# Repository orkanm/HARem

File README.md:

# HARem - Home Assistant Remote Controller

**HARem** is a high-performance, minimalist "Thin Client" remote controller designed for the modern smart home. Built on the **ESPHome** ecosystem and powered by the **ESP32-C3**, it provides a boutique-quality physical interface that prioritizes speed, aesthetics, and zero-maintenance operation.

---

## ✨ Features & Architecture

Unlike traditional smart remotes that require manual configuration of every button, HARem operates as a **dynamic viewport** into your Home Assistant instance. Complex logic is handled by Home Assistant Blueprints and Automations, keeping the hardware lightweight and responsive.

- **Zero Maintenance**: Rooms, devices, and states are streamed in real-time. New devices added to a Home Assistant Area automatically appear on the remote.
- **Modern UI**: A 5-line **1.3" OLED** interface featuring Outfit and Montserrat typography, a vertical scrollbar, and hardware-accelerated dynamic marquee for long names.
- **Smart Power**: Deep sleep optimized for sub-1mA idle consumption, utilizing a high-impedance (1MΩ/1MΩ) battery divider and active OLED power management.
- **Guest Mode Protection**: Secure, PIN-protected "Guest Mode" to restrict access to specific areas or devices.
- **Visual Feedback & Control**: Interactive animations, sleep countdowns, and a local on-device menu for contrast and standby settings.

---

## 🚀 Quick Start

1. **Hardware**: ESP32-C3 SuperMini + 1.3" SH1106 OLED + EC11 Rotary Encoder.
2. **Firmware**: 
    * **Option A (Recommended)**: Download the latest **`.factory.bin`** from [Releases](https://github.com/orkanm/HARem/releases) and flash it to **offset 0x0**.
    * **Option B**: Compile locally using `esphome run remote_controller.yaml`.
3. **Home Assistant**: 
    * The device will appear as "HARem" in your dashboard.
    * **IMPORTANT**: If you used the GitHub Release binary, you will be asked for an **Encryption Key**:
        > `7knRB3/EL4Fq8Foul7Yhv+pcABzyLXHSQxa9bTzzQqg=`
    * > [!WARNING]
      > This key is **publicly known**. For security, you should change it in your own configuration and perform an [OTA update](https://esphome.io/components/ota.html) as soon as possible.
    * Follow the [Setup Guide](docs/generic_menu_setup.md) to create the required Helpers and import the logic Blueprint.

---

## 🛠️ Hardware & Assembly

Building your own HARem is straightforward. The project includes custom PCB files and 3D printable case models.

### Interactive Visualizers
Explore the design files directly in your browser:
* **[Interactive PCB 3D Viewer](https://3dviewer.net/index.html#model=https://raw.githubusercontent.com/orkanm/HARem/main/PCB/HARem/HArem.step)** (STEP format)
* **[Interactive Case 3D Viewer](https://3dviewer.net/index.html#model=https://raw.githubusercontent.com/orkanm/HARem/main/Case/HARem_Case_2.0-Case.stl,https://raw.githubusercontent.com/orkanm/HARem/main/Case/HARem_Case_2.0-Lid.stl,https://raw.githubusercontent.com/orkanm/HARem/main/Case/Encoder_Knob.stl)** (STL format)
* **[Interactive Schematic](https://kicanvas.org/?github=https://github.com/orkanm/HARem/blob/main/PCB/HARem/HArem.kicad_sch)**
* **[Interactive PCB Layout](https://kicanvas.org/?github=https://github.com/orkanm/HARem/blob/main/PCB/HARem/HArem.kicad_pcb)**

### Design Files
* **[KiCad Project](PCB/HARem/)**: Source files for schematic and board layout.
* **[PCB 3D Model](PCB/HARem/HArem.step)**: Industrial standard 3D file for enclosure design.
* **[3D Printed Case Files](Case/)**: Source FreeCAD project (`.FCStd`), print-ready `.stl` files for the case, lid, and knob, along with a high-resolution `.step` model.

<details>
<summary><b>View Wiring Diagram & Pin Mapping (Click to expand)</b></summary>

```text
       ESP32-C3 Super Mini                 Peripherals
    ┌───────────────────────┐            ┌───────────────┐
    │                       │   Q1(NPN)  │ 1.3" OLED     │
    │          5V / 3.3V ───┼────▶[C]    │               │
    │  GPIO1 (OLED PWR) ────┼────▶[B]    │               │
    │                       │     [E]────┼─▶ [VCC]       │
    │                GND ───┼────────────┼─▶ [GND]       │
    │         GPIO5 (SDA)───┼────────────┼─▶ [SDA]       │
    │         GPIO6 (SCL)───┼────────────┼─▶ [SCL]       │
    │                       │            └───────────────┘
    │                       │            
    │                       │            ┌───────────────┐
    │                       │            │ ROTARY (EC11) │
    │         GPIO8 (CLK) ◀─┼───[100Ω]───┼─ [CLK]        │
    │          GPIO9 (DT) ◀─┼───[100Ω]───┼─ [DT]         │
    │          GPIO4 (SW) ◀─┼───[100Ω]───┼─ [SW]         │
    │                GND  ◀─┼────────────┼─ [GND]        │
    │                       │            └───────────────┘
    │                       │            ┌───────────────┐
    │                       │            │ BAT MONITOR   │
    │                       │            │  [+] BATTERY  │
    │                       │            │   │           │
    │                       │            │  [1MΩ]        │
    │         GPIO0 (ADC) ◀─┼────────────┼───┤           │
    │                       │            │  [1MΩ] [0.1µF]│
    │                       │            │   │      │    │
    │                GND  ◀─┼────────────┼──GND────GND   │
    └───────────────────────┘            └───────────────┘
```

| Component | ESP32-C3 Pin | Type | Notes |
| :--- | :--- | :--- | :--- |
| **OLED VCC** | GPIO1 | Output | Active Power Management (via Q1 NPN) |
| **OLED SDA/SCL** | GPIO5 / GPIO6 | I2C | SSD1306/SH1106 |
| **Encoder CLK/DT** | GPIO8 / GPIO9 | Input | Navigation |
| **Encoder SW** | GPIO4 | Input | Wakeup Trigger |
| **Battery ADC** | GPIO0 | Analog | 1M/1M Divider + 0.1µF Cap |

</details>

---

## 📖 Documentation & Development

* **[Behavior & Interaction Map](docs/behavior_map.md)**: Visual state machines and logic flows for the device interaction.
* **[Project Walkthrough](docs/walkthrough.md)**: Architecture, features, and troubleshooting.
* **[Home Assistant Setup Guide](docs/generic_menu_setup.md)**: How to configure the Home Assistant side.
* **[Environment Installation & Setup Guide](docs/installation.md)**: Guide for setting up your local Python environment and secrets.
* **[Roadmap](TODO.md)**: Planned improvements and future features.

---

## 📛 Trivia: The Name HARem

The name **HARem** is a clever portmanteau of **H**ome **A**ssistant and **Rem**ote, but its inspiration runs deeper into Turkish history and culture. 

In Turkish and Ottoman history, the **Harem** represented the most private, sacred, and protected part of the household. By adopting this name, the project acknowledges the smart home as the modern individual's "inner sanctum." Just as the historical Harem was the heart of the home, this remote serves as the private, primary interface to control and protect the sanctity of your living space.

---

## ☕ Support the Project

If you find this project helpful and would like to support its development, you can buy me a coffee! Your support helps fund new prototypes and keeps the project open-source and free for everyone.

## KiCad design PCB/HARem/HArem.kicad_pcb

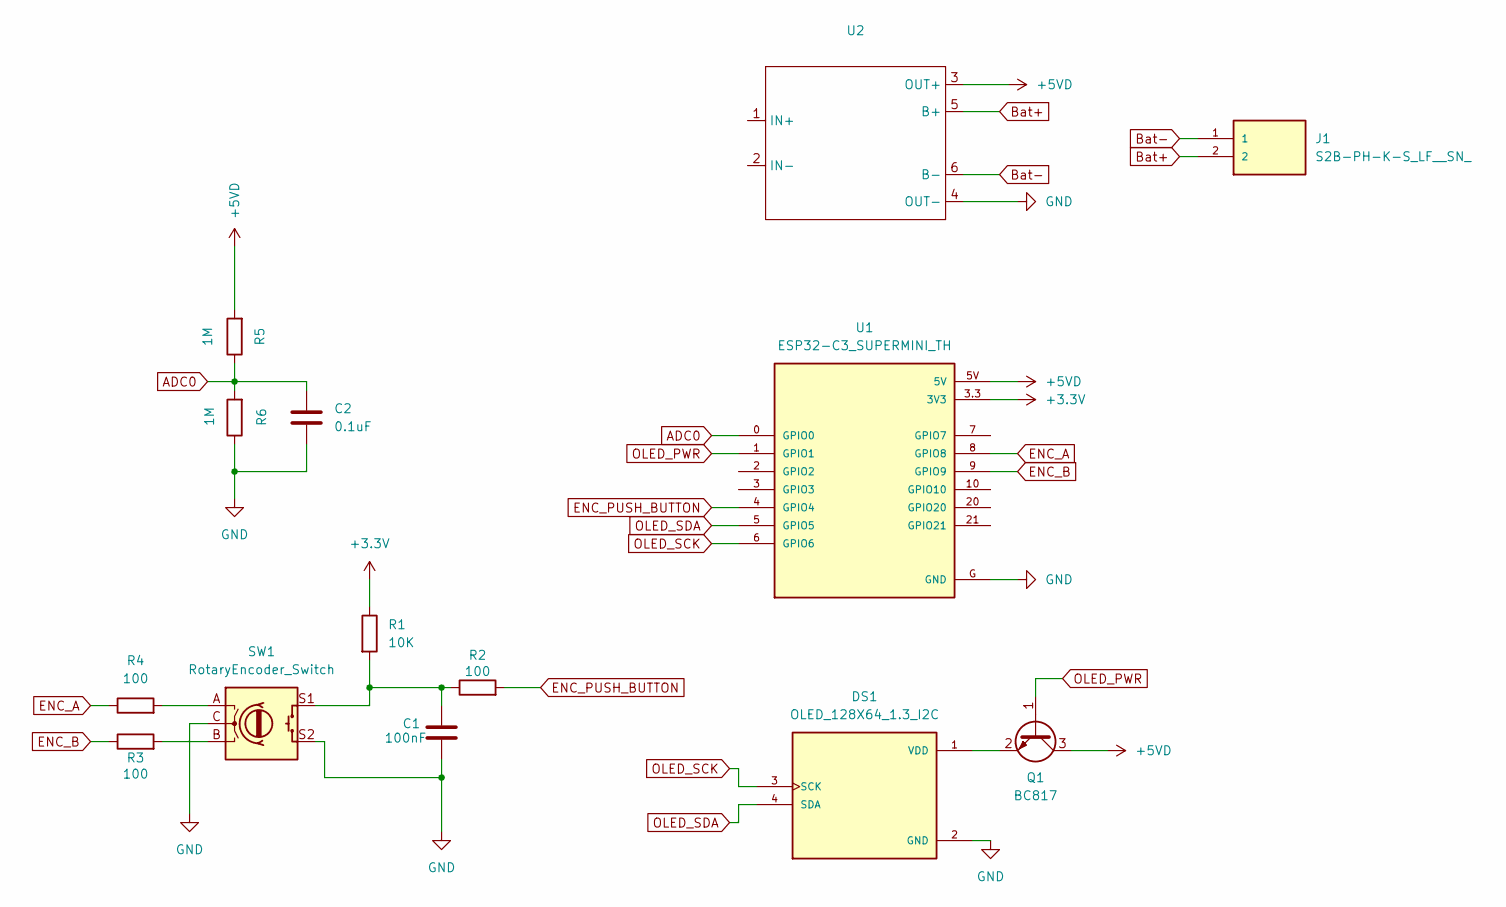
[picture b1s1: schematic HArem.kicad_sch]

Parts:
C1: 100nF; C_0805_2012Metric
C2: 0.1uF; C_0805_2012Metric
DS1: OLED_128X64_1.3_I2C; LCD_OLED_128X64_1.3_I2C; PARTREV NA
J1: S2B-PH-K-S_LF__SN_; JST_S2B-PH-K-S_LF__SN_
Q1: BC817; SOT-23
R1: 10K; R_0805_2012Metric
R2, R3, R4: 100; R_0805_2012Metric
R5, R6: 1M; R_0805_2012Metric
SW1: RotaryEncoder_Switch; RotaryEncoder_Alps_EC11E-Switch_Vertical_H20mm_MountingHoles
U1: ESP32-C3_SUPERMINI_TH; MODULE_ESP32-C3_SUPERMINI_TH
U2: TP4056-Module

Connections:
+3.3V: R1.1, U1.3.3 (3V3)
+5VD: Q1.3 (C), R5.2, U1.5V, U2.3 (OUT+)
ADC0: C2.1, R5.1, R6.2, U1.0 (GPIO0)
Bat+: J1.2, U2.5 (B+)
Bat-: J1.1, U2.6 (B-)
ENC_A: R4.1, U1.8 (GPIO8)
ENC_B: R3.1, U1.9 (GPIO9)
ENC_PUSH_BUTTON: R2.2, U1.4 (GPIO4)
GND: C1.2, C2.2, DS1.2 (GND), R6.1, SW1.C, SW1.S2, U1.G (GND), U2.4 (OUT-)
unnamed: C1.1, R1.2, R2.1, SW1.S1
unnamed: DS1.1 (VDD), Q1.2 (E)
unnamed: R3.2, SW1.B
unnamed: R4.2, SW1.A
OLED_PWR: Q1.1 (B), U1.1 (GPIO1)
OLED_SCK: DS1.3 (SCK), U1.6 (GPIO6)
OLED_SDA: DS1.4 (SDA), U1.5 (GPIO5)

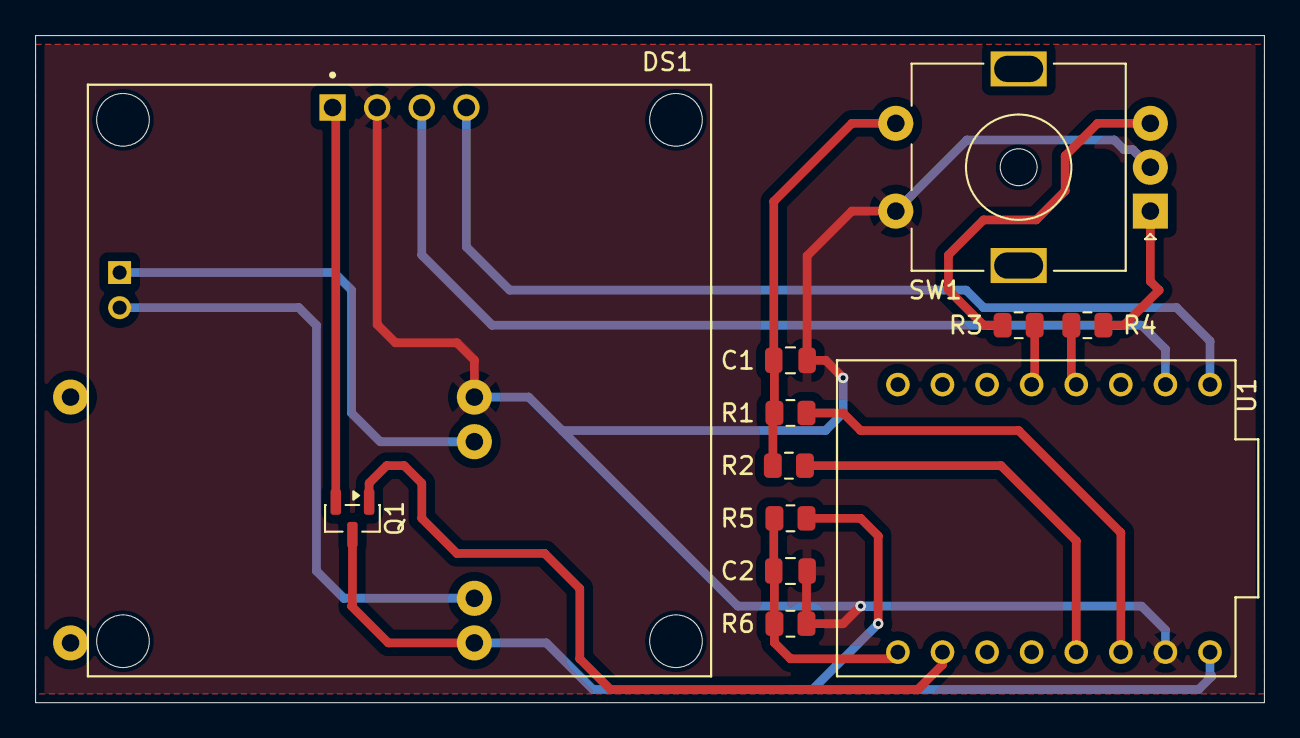
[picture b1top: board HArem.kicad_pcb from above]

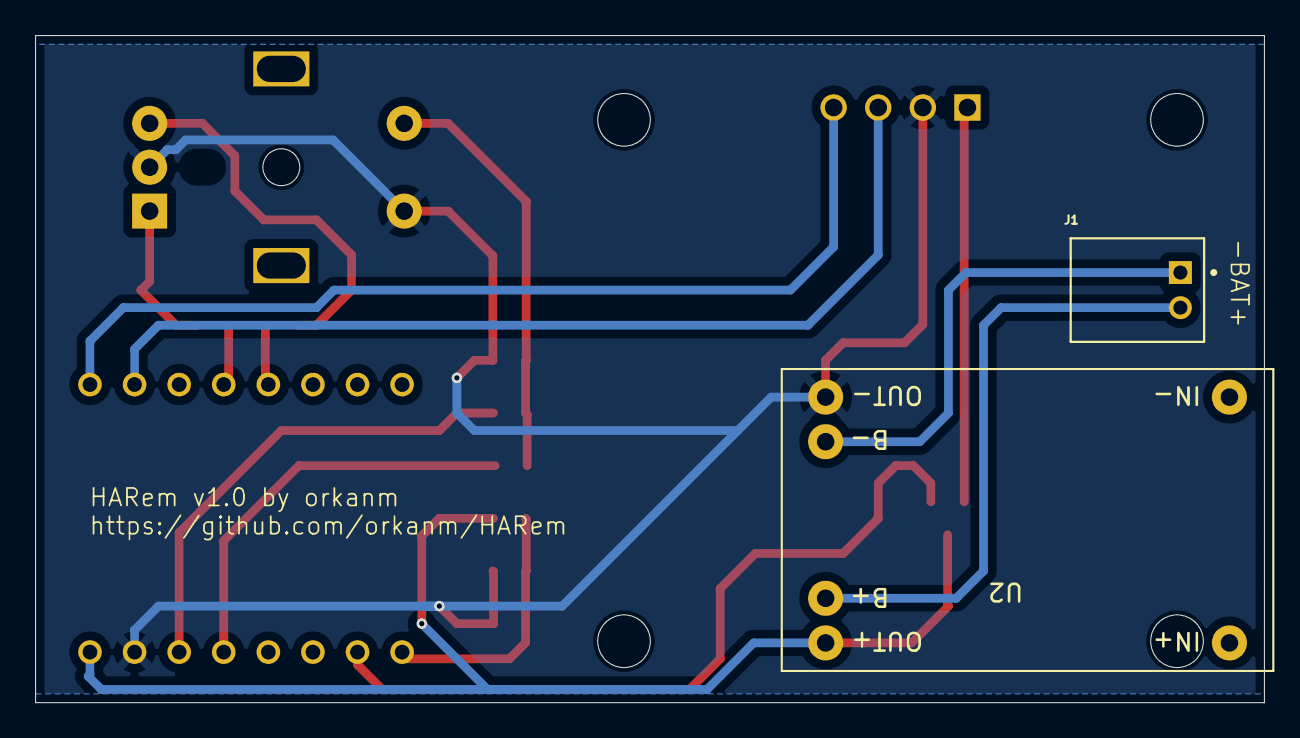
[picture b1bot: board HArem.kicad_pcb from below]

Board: 2 copper layers, 70.0 x 38.0 mm, 14 parts (2 on the bottom side), 16 nets.

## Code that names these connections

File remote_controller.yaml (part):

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
# I2C Configuration for OLED
i2c:
  sda: GPIO5
  scl: GPIO6
  frequency: 900kHz
  scan: true
  id: bus_a
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
  - platform: gpio
    pin:
      number: GPIO4
      mode: INPUT_PULLUP
      allow_other_uses: true
      inverted: true
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  - platform: rotary_encoder
    id: encoder
    pin_a:
      number: GPIO9
      mode: INPUT_PULLUP
    pin_b:
      number: GPIO8
      mode: INPUT_PULLUP
    resolution: 1
    on_clockwise:
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    update_interval: 60s

  - platform: adc
    pin: GPIO0
    name: "Battery Voltage"
    id: battery_voltage_adc
    update_interval: 60s
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  id: sleep_module
  sleep_duration: 1d
  wakeup_pin:
    number: GPIO4
    inverted: true
    mode: INPUT_PULLUP
    allow_other_uses: true
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          id(sleep_countdown) = -1;
          id(my_display).turn_off();
          id(oled_power).turn_off();
          // Lock OLED Power Pin LOW during Deep Sleep (ONLY GPIO1)
          gpio_hold_en(GPIO_NUM_1);
      - logger.log: "Entering Deep Sleep..."
      - deep_sleep.enter: sleep_module
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switch:
  - platform: gpio
    pin: 
      number: GPIO1
      drive_strength: 40mA
    id: oled_power
    restore_mode: ALWAYS_ON
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
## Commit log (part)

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2025-12-31 Initial commit: ESPHome Remote Controller with 5-line generic menu
2025-12-31 Update README with documentation links and feature list
2026-01-01 Fix: Rotary dir, entity filter, and toggle delay
2026-01-01 Refactor: Enhanced startup sequence and documentation fixes
2026-01-01 Fix: Update firmware version text to v0.1
2026-01-01 Refactor: Move firmware version to substitutions block
2026-01-01 Fix: Remove click dead zone (800ms split)
2026-01-01 Fix: Set click timing to 300ms split per user request
2026-01-02 Finalize Settings Menu and Documentation
2026-01-02 Add GitHub Actions for Build and Release
2026-01-02 Fix deprecated actions versions
2026-01-02 Move AP password to secrets.yaml
2026-01-02 Add Hotspot Display Feature
2026-01-02 Fix CI invalid Base64 key format
2026-01-02 Sync Hotspot Display password with rotated secrets
2026-01-02 Update walkthrough with correct hotspot password
2026-01-03 Finalize documentation with One-Click Package and Blueprint options
2026-01-03 Bump version to v0.2 and add changelog
2026-01-03 refactor: optimize button interaction using manual timing logic
2026-01-03 feat: implement instant 5s settings trigger and two-way exit logic
2026-01-03 feat: implement circular visual wrapping for settings menu
2026-01-03 feat: battery support, deep sleep, visual countdown, and optimized settings defaults
2026-01-03 feat: add smooth sleep animations and UI polish
2026-01-03 feat: implement global animation toggle in settings
2026-01-03 feat: complete animation toggle implementation
2026-01-03 fix: resolve animation toggle persistence issue
2026-01-03 docs: consolidate project information into README
2026-01-03 docs: clear overlaps between README and ABOUT
2026-01-03 docs: merge ABOUT.md into README for a unified landing page
2026-01-03 docs: consolidate hardware wiring into README and remove redundant schematic files
2026-01-14 feat(v0.6.0): Guest Mode PIN Security & Sleep Logic Fix
2026-01-14 feat(security): Implement On-Device PIN Change & Default to 00
2026-01-14 chore: Bump version to v0.6.0-test
2026-01-14 Feature: Enhanced UI, Persistence Fixes & Multi-Device Guest Mode
    - Implemented absolute percentage feedback (0-100%) in overlay.
    - Removed progress bar for cleaner text-only interface.
    - Fixed menu persistence on fast 'Press & Twist' interactions.
    - Added support for multiple devices in Guest Mode selector.
    - Refactored blueprint state logic for stability.
2026-01-20 optimize: Fix deep sleep drain (SuperMini 0.9mA), lock GPIO7, update TODOs
2026-01-27 Add hardware pinout documentation with wiring diagram
2026-01-27 Update voltage divider design to Ultra Low Power (1MΩ + Cap)
2026-02-11 Fix: Reverse encoder pins, fix stuck screen on boot, improve wake-up logic
2026-02-12 Add MIT License
2026-02-12 Add Buy Me a Coffee support links to README
2026-02-12 Update documentation to match latest hardware (v1.0) and restore 1M battery divider
2026-02-12 docs: add interactive 3D PCB viewer link
2026-02-12 docs: list Orkan Murat Celik as the maintainer
2026-02-12 chore: bump version to v0.6.1-test
2026-02-12 docs: remove unnecessary GLB assets and update project documentation
2026-02-12 docs: integrate interactive design visualizers and finalize cleanup
2026-02-12 chore: update .gitignore to exclude KiCad local files
2026-02-12 chore: ignore ESP32-C3_SUPERMINI_TH folder
2026-02-12 docs: document low power consumption features
2026-02-12 chore: fix github language detection via .gitattributes
2026-02-12 chore: attempt esphome language label and add badge
2026-02-12 chore: consolidate WiFi configuration and remove duplicates
2026-02-12 chore: fix dashboard_import and verify compilation
2026-02-12 fix: provide factory firmware image for ESP-IDF builds
2026-02-12 docs: add security warning for release encryption key
2026-02-12 feat: add WiFi signal indicator to settings page
2026-02-12 Refactor: Change sleep transition to 3x flicker
2026-02-14 docs: add HARem case files and documentation
2026-02-15 Add updated 3D drawings for HARem case
2026-02-15 Update README with correct filenames and 3D viewer links
2026-02-15 Fix Guest Mode toggle behavior in settings menu
2026-02-20 fix(sleep): resolve flicker and crash by simplifying idle timer
2026-02-24 Fix display flickering on wake up
2026-02-28 Update fw_version to v0.6.2-Fix
2026-02-28 ci: automate dependency updates with dependabot
2026-02-28 chore(deps): bump actions/upload-artifact from 4 to 7
    Bumps [actions/upload-artifact](https://github.com/actions/upload-artifact) from 4 to 7.
    - [Release notes](https://github.com/actions/upload-artifact/releases)
    - [Commits](https://github.com/actions/upload-artifact/compare/v4...v7)
    ---
    updated-dependencies:
    - dependency-name: actions/upload-artifact
2026-02-28 chore(deps): bump actions/download-artifact from 4 to 8
    Bumps [actions/download-artifact](https://github.com/actions/download-artifact) from 4 to 8.
    - [Release notes](https://github.com/actions/download-artifact/releases)
    - [Commits](https://github.com/actions/download-artifact/compare/v4...v8)
    ---
    updated-dependencies:
    - dependency-name: actions/download-artifact
2026-02-28 chore(deps): bump actions/checkout from 4 to 6
    Bumps [actions/checkout](https://github.com/actions/checkout) from 4 to 6.
    - [Release notes](https://github.com/actions/checkout/releases)
    - [Changelog](https://github.com/actions/checkout/blob/main/CHANGELOG.md)
    - [Commits](https://github.com/actions/checkout/compare/v4...v6)
    ---
    updated-dependencies:
2026-03-07 chore(deps): bump esphome from 2026.2.2 to 2026.2.4
    Bumps [esphome](https://github.com/esphome/esphome) from 2026.2.2 to 2026.2.4.
    - [Release notes](https://github.com/esphome/esphome/releases)
    - [Commits](https://github.com/esphome/esphome/compare/2026.2.2...2026.2.4)
    ---
    updated-dependencies:
    - dependency-name: esphome
2026-03-07 Version number fix.
2026-03-21 chore(deps): bump esphome from 2026.2.4 to 2026.3.0
    Bumps [esphome](https://github.com/esphome/esphome) from 2026.2.4 to 2026.3.0.
    - [Release notes](https://github.com/esphome/esphome/releases)
    - [Commits](https://github.com/esphome/esphome/compare/2026.2.4...2026.3.0)
    ---
    updated-dependencies:
    - dependency-name: esphome
2026-04-04 chore(deps): bump esphome from 2026.3.1 to 2026.3.2
    Bumps [esphome](https://github.com/esphome/esphome) from 2026.3.1 to 2026.3.2.
    - [Release notes](https://github.com/esphome/esphome/releases)
    - [Commits](https://github.com/esphome/esphome/compare/2026.3.1...2026.3.2)
    ---
    updated-dependencies:
    - dependency-name: esphome
2026-04-11 chore(deps): bump esphome from 2026.3.2 to 2026.3.3
    Bumps [esphome](https://github.com/esphome/esphome) from 2026.3.2 to 2026.3.3.
    - [Release notes](https://github.com/esphome/esphome/releases)
    - [Commits](https://github.com/esphome/esphome/compare/2026.3.2...2026.3.3)
    ---
    updated-dependencies:
    - dependency-name: esphome
2026-04-11 fix: stale line_5 display, instant-entity overlay, and 3s toggle timeout
    - remote_controller.yaml: guard line_4/line_5 rendering with empty-string
    check to prevent stale room names showing after navigation
    - harem_package.yaml: reduce toggle wait timeout from 10s to 3s
    - blueprints/harem_remote.yaml: same 3s timeout reduction; skip wait for
    instant-action entities (scene/script/button) which never produce a
    detectable state change, showing 'Activating...' for 1s instead of
2026-04-11 docs: update CHANGELOG for v0.6.3 bug fixes
2026-04-12 Fix brightness adjustment latency and display lag in control mode
    * Changed blueprint automation mode to 'restart' to eliminate event queue backlog and latency during rapid encoder spins.
    * Changed send_rotate_cw/ccw_hold_event scripts to 'mode: single' to prevent redundant idle_timer restarts.
    * Reordered rotate_hold sequence so line_5 percentage and overlay update *before* the light/media service call, ensuring the screen stays perfectly responsive even if intermediate runs are restarted.
    * Changed relative brightness/volume steps to absolute values using the accumulated line_5 tracker, ensuring the final light state perfectly matches the screen display.
    * Wrapped the line_1-5 display upda
2026-04-12 fix(dimming): overhaul dirigera bypass, debouncing interrupts, and grid-snapping math
2026-04-13 Untrack code_review.md and add to .gitignore
2026-04-15 Fix UI state persistence and timeout for slower networks
    - Increased blueprint wait_template timeout from 3s to 5s to stop 'Failed!' overlays on slower Matter/Thread smart devices.
    - Added background refresh event to firmware to forcefully sync stale caching states when waking from screen standby or deep sleep.
    - Updated CHANGELOG to reflect fixes.
2026-04-18 chore(deps): bump esphome from 2026.3.3 to 2026.4.0
    Bumps [esphome](https://github.com/esphome/esphome) from 2026.3.3 to 2026.4.0.
    - [Release notes](https://github.com/esphome/esphome/releases)
    - [Commits](https://github.com/esphome/esphome/compare/2026.3.3...2026.4.0)
    ---
    updated-dependencies:
    - dependency-name: esphome
2026-04-19 Fix PCB folder name capitalization and ignore cache/review file
2026-04-25 chore(deps): bump esphome from 2026.4.0 to 2026.4.2
    Bumps [esphome](https://github.com/esphome/esphome) from 2026.4.0 to 2026.4.2.
    - [Release notes](https://github.com/esphome/esphome/releases)
    - [Commits](https://github.com/esphome/esphome/compare/2026.4.0...2026.4.2)
    ---
    updated-dependencies:
    - dependency-name: esphome
2026-04-26 Installation document is added.
2026-05-02 chore(deps): bump esphome from 2026.4.2 to 2026.4.3
    Bumps [esphome](https://github.com/esphome/esphome) from 2026.4.2 to 2026.4.3.
    - [Release notes](https://github.com/esphome/esphome/releases)
    - [Commits](https://github.com/esphome/esphome/compare/2026.4.2...2026.4.3)
    ---
    updated-dependencies:
    - dependency-name: esphome
2026-05-02 Docs: Update README, CHANGELOG, and Walkthrough for v0.7.0 UI redesign
2026-05-08 Fix battery percentage, deep sleep, and overlay errors
2026-05-23 chore(deps): bump esphome from 2026.4.5 to 2026.5.0
    Bumps [esphome](https://github.com/esphome/esphome) from 2026.4.5 to 2026.5.0.
    - [Release notes](https://github.com/esphome/esphome/releases)
    - [Commits](https://github.com/esphome/esphome/compare/2026.4.5...2026.5.0)
    ---
    updated-dependencies:
    - dependency-name: esphome
2026-05-30 chore(deps): bump esphome from 2026.5.0 to 2026.5.1
    Bumps [esphome](https://github.com/esphome/esphome) from 2026.5.0 to 2026.5.1.
    - [Release notes](https://github.com/esphome/esphome/releases)
    - [Commits](https://github.com/esphome/esphome/compare/2026.5.0...2026.5.1)
    ---
    updated-dependencies:
    - dependency-name: esphome
2026-06-06 chore(deps): bump esphome from 2026.5.1 to 2026.5.3
    Bumps [esphome](https://github.com/esphome/esphome) from 2026.5.1 to 2026.5.3.
    - [Release notes](https://github.com/esphome/esphome/releases)
    - [Commits](https://github.com/esphome/esphome/compare/2026.5.1...2026.5.3)
    ---
    updated-dependencies:
    - dependency-name: esphome
2026-06-20 chore(deps): bump esphome from 2026.5.3 to 2026.6.1
    Bumps [esphome](https://github.com/esphome/esphome) from 2026.5.3 to 2026.6.1.
    - [Release notes](https://github.com/esphome/esphome/releases)
    - [Commits](https://github.com/esphome/esphome/compare/2026.5.3...2026.6.1)
    ---
    updated-dependencies:
    - dependency-name: esphome
2026-06-27 chore(deps): bump esphome from 2026.5.3 to 2026.6.2
    Bumps [esphome](https://github.com/esphome/esphome) from 2026.5.3 to 2026.6.2.
    - [Release notes](https://github.com/esphome/esphome/releases)
    - [Commits](https://github.com/esphome/esphome/compare/2026.5.3...2026.6.2)
    ---
    updated-dependencies:
    - dependency-name: esphome
